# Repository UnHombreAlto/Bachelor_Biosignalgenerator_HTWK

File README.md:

# Bachelor_Biosignalgenerator_HTWK
Sammlung des Materials zur Bachelorarbeit Biosignalgenerator

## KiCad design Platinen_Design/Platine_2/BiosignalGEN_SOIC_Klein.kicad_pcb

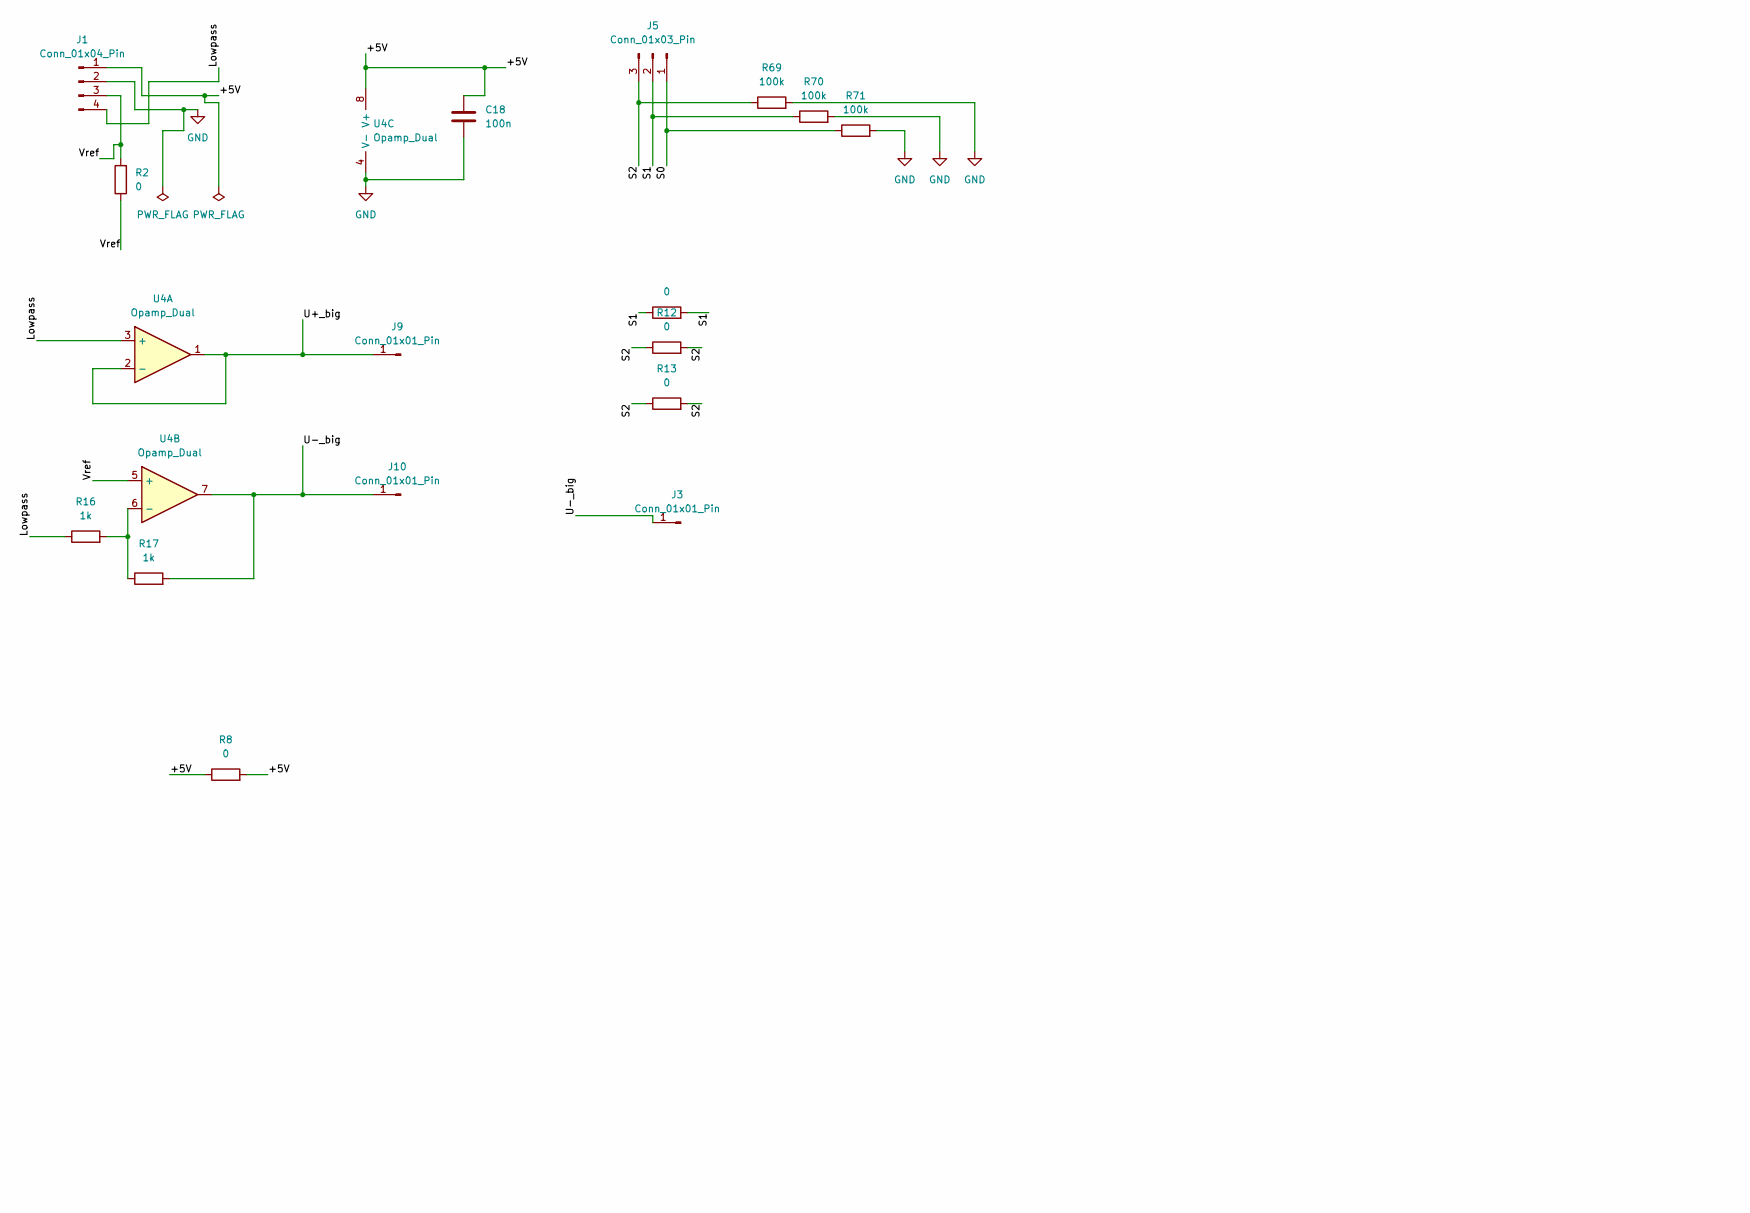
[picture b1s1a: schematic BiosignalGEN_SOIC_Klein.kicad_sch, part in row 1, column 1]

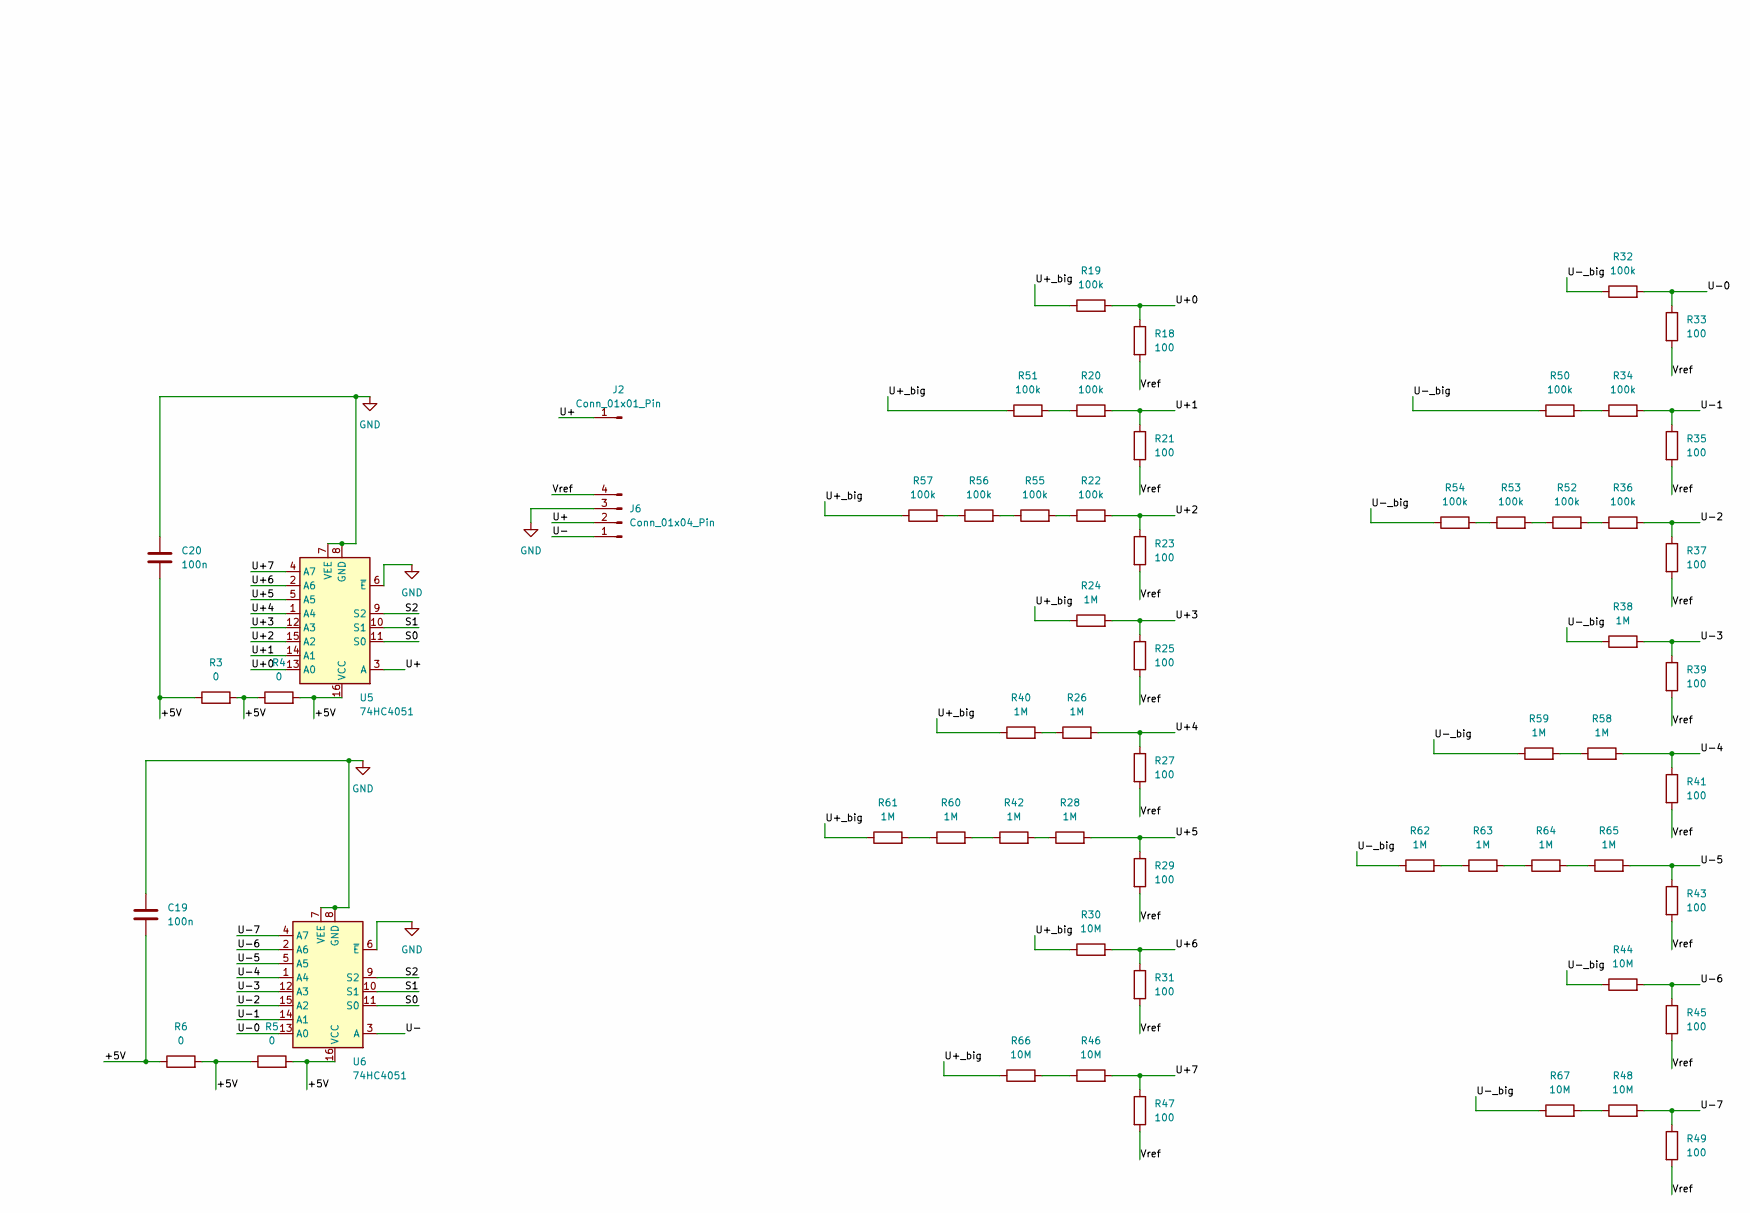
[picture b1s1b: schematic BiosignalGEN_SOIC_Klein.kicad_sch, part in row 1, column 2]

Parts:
C18, C19, C20: 100n; C_1206_3216Metric_Pad1.33x1.80mm_HandSolder
J1, J6: Conn_01x04_Pin; PinHeader_1x04_P2.54mm_Vertical
J2, J3, J9, J10: Conn_01x01_Pin; PinHeader_1x01_P2.54mm_Vertical
J5: Conn_01x03_Pin; PinHeader_1x03_P2.54mm_Vertical
R2, R3, R4, R5, R6, R8, R11, R12, R13: 0; R_1206_3216Metric_Pad1.30x1.75mm_HandSolder
R16, R17: 1k; R_1206_3216Metric_Pad1.30x1.75mm_HandSolder
R18, R21, R23, R25, R27, R29, R31, R33, R35, R37, R39, R41, R43, R45, R47, R49: 100; R_1206_3216Metric_Pad1.30x1.75mm_HandSolder
R19, R20, R22, R32, R34, R36, R50, R51, R52, R53, R54, R55, R56, R57, R69, R70, R71: 100k; R_1206_3216Metric_Pad1.30x1.75mm_HandSolder
R24, R26, R28, R38, R40, R42, R58, R59, R60, R61, R62, R63, R64, R65: 1M; R_1206_3216Metric_Pad1.30x1.75mm_HandSolder
R30, R44, R46, R48, R66, R67: 10M; R_1206_3216Metric_Pad1.30x1.75mm_HandSolder
U4: Opamp_Dual; SOIC-8_3.9x4.9mm_P1.27mm
U5, U6: 74HC4051; SO-16_3.9x9.9mm_P1.27mm

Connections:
/+5V: C18.1, C19.2, C20.2, J1.1, R3.1, R3.2, R4.1, R4.2, R5.1, R5.2, R6.1, R6.2, R8.1, R8.2, U4.8 (V+), U5.16 (VCC), U6.16 (VCC)
/Lowpass: J1.4, R16.1, U4.3 (+)
/S0: J5.1, R71.1, U5.11 (S0), U6.11 (S0)
/S1: J5.2, R11.1, R11.2, R70.1, U5.10 (S1), U6.10 (S1)
/S2: J5.3, R12.1, R12.2, R13.1, R13.2, R69.1, U5.9 (S2), U6.9 (S2)
/U+: J2.1 (Pin_1_1), J6.2, U5.3 (A)
/U+0: R18.1, R19.2, U5.13 (A0)
/U+1: R20.2, R21.1, U5.14 (A1)
/U+2: R22.2, R23.1, U5.15 (A2)
/U+3: R24.2, R25.1, U5.12 (A3)
/U+4: R26.2, R27.1, U5.1 (A4)
/U+5: R28.2, R29.1, U5.5 (A5)
/U+6: R30.2, R31.1, U5.2 (A6)
/U+7: R46.2, R47.1, U5.4 (A7)
/U+_big: J9.1 (Pin_1_1), R19.1, R24.1, R30.1, R40.1, R51.1, R57.1, R61.1, R66.1, U4.1, U4.2 (-)
/U-: J6.1, U6.3 (A)
/U-0: R32.2, R33.1, U6.13 (A0)
/U-1: R34.2, R35.1, U6.14 (A1)
/U-2: R36.2, R37.1, U6.15 (A2)
/U-3: R38.2, R39.1, U6.12 (A3)
/U-4: R41.1, R58.2, U6.1 (A4)
/U-5: R43.1, R65.2, U6.5 (A5)
/U-6: R44.2, R45.1, U6.2 (A6)
/U-7: R48.2, R49.1, U6.4 (A7)
/U-_big: J3.1 (Pin_1_1), J10.1 (Pin_1_1), R17.2, R32.1, R38.1, R44.1, R50.1, R54.1, R59.1, R62.1, R67.1, U4.7
/Vref: J1.3, J6.4, R2.1, R2.2, R18.2, R21.2, R23.2, R25.2, R27.2, R29.2, R31.2, R33.2, R35.2, R37.2, R39.2, R41.2, R43.2, R45.2, R47.2, R49.2, U4.5 (+)
GND: C18.2, C19.1, C20.1, J1.2, J6.3, R69.2, R70.2, R71.2, U4.4 (V-), U5.6 (~E), U5.7 (VEE), U5.8 (GND), U6.6 (~E), U6.7 (VEE), U6.8 (GND)
unnamed: R20.1, R51.2
unnamed: R22.1, R55.2
unnamed: R26.1, R40.2
unnamed: R28.1, R42.2
unnamed: R34.1, R50.2
unnamed: R36.1, R52.2
unnamed: R42.1, R60.2
unnamed: R46.1, R66.2
unnamed: R48.1, R67.2
unnamed: R52.1, R53.2
unnamed: R53.1, R54.2
unnamed: R55.1, R56.2
unnamed: R56.1, R57.2
unnamed: R58.1, R59.2
unnamed: R60.1, R61.2
unnamed: R62.2, R63.1
unnamed: R63.2, R64.1
unnamed: R64.2, R65.1
unnamed: R16.2, R17.1, U4.6 (-)

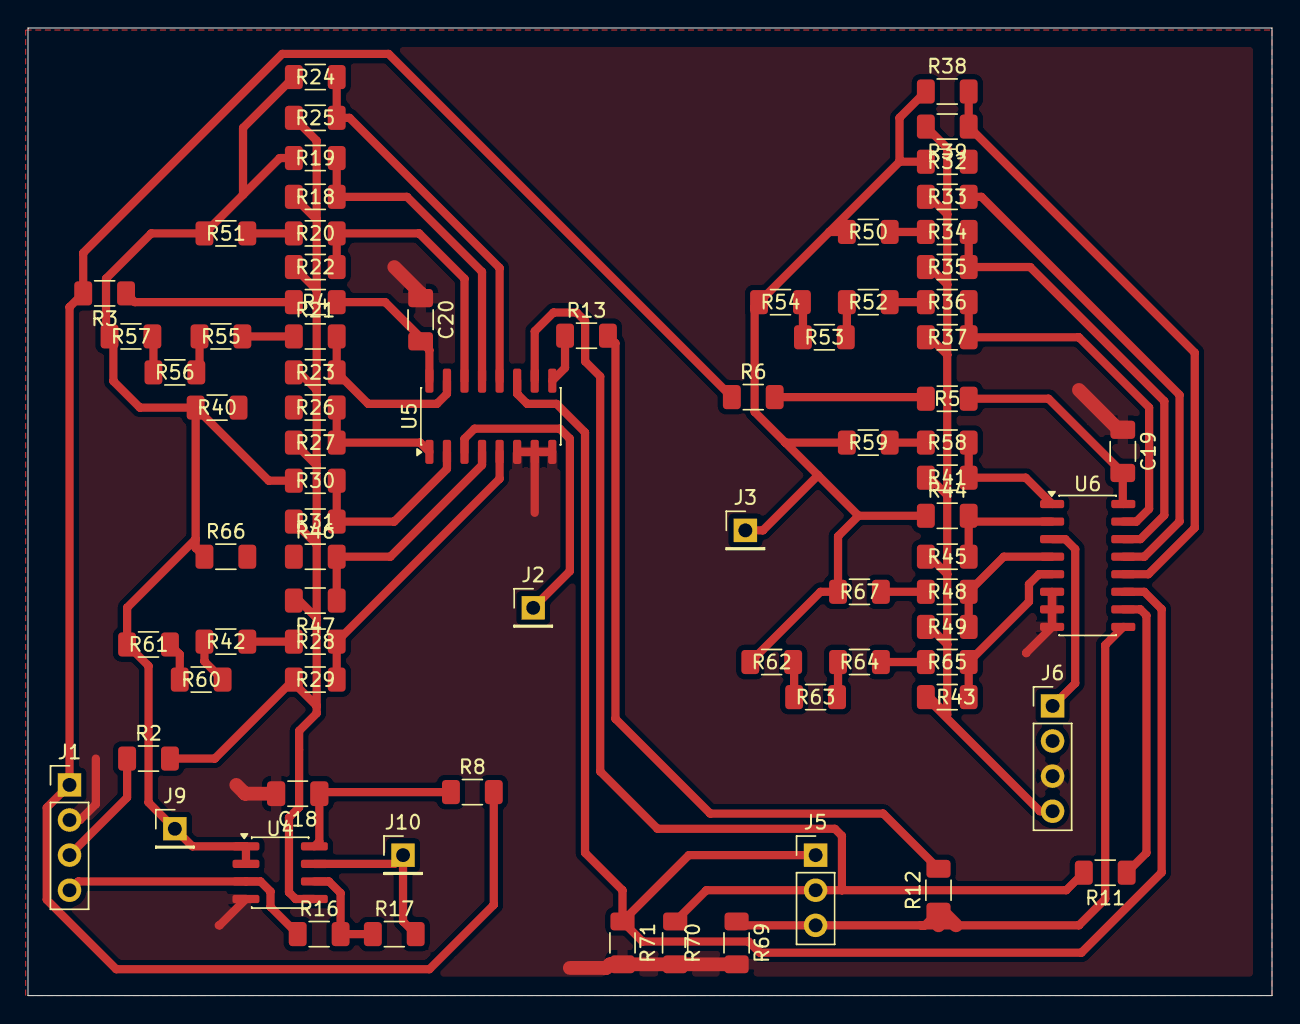
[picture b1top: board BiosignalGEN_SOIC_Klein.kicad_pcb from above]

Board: 2 copper layers, 90.0 x 70.0 mm, 77 parts (0 on the bottom side), 46 nets.

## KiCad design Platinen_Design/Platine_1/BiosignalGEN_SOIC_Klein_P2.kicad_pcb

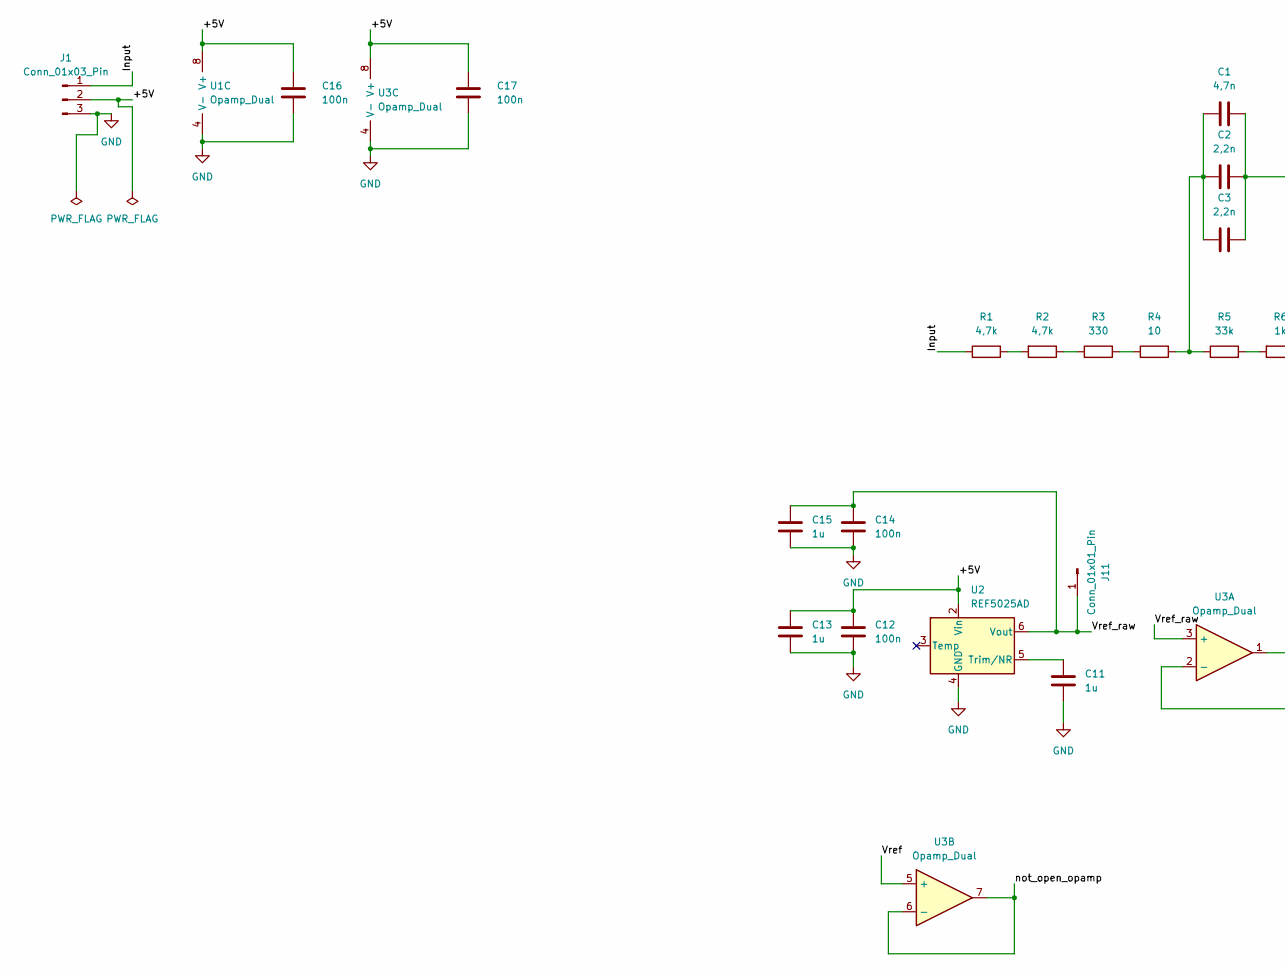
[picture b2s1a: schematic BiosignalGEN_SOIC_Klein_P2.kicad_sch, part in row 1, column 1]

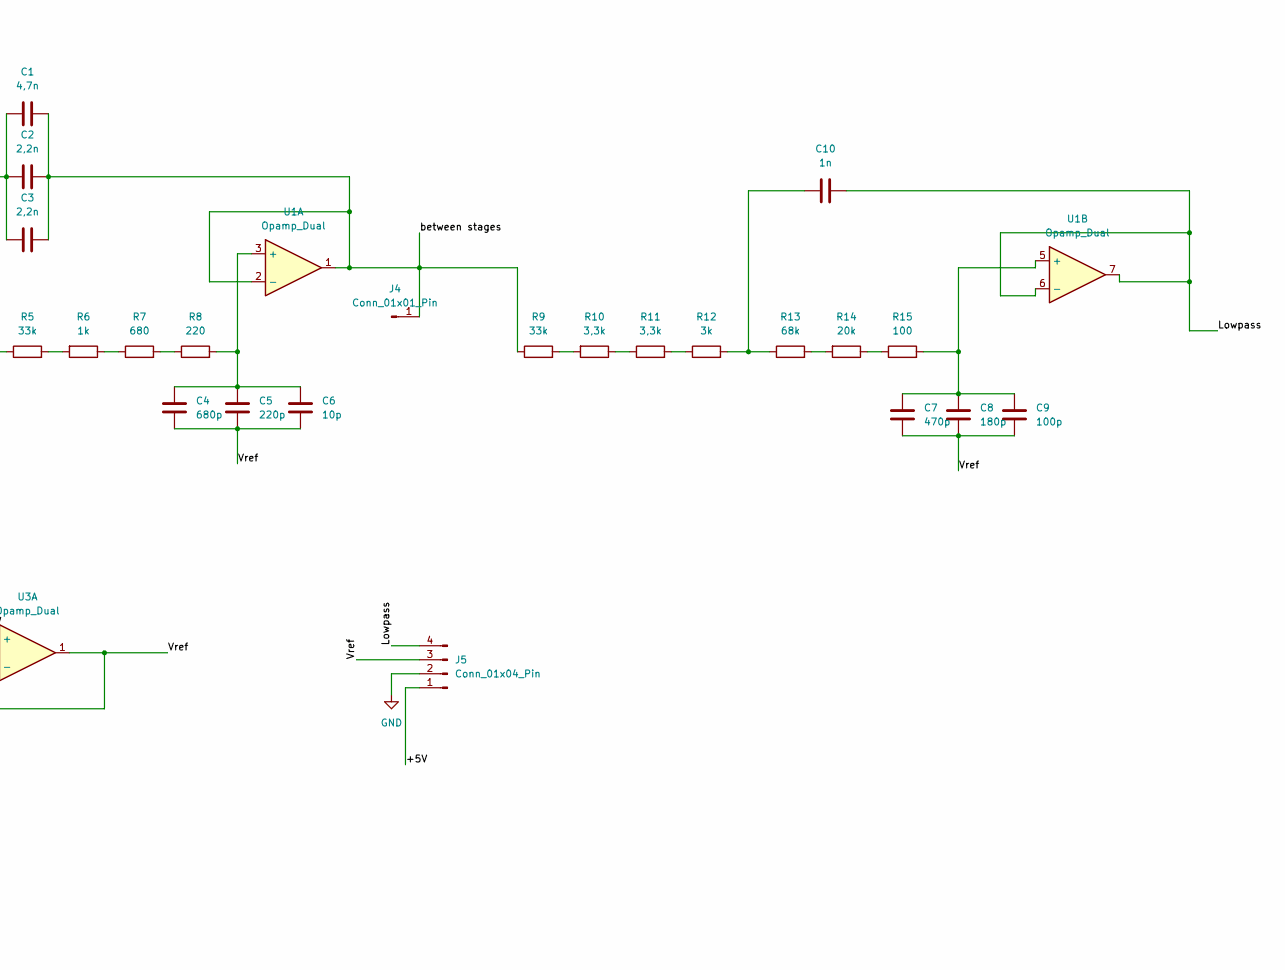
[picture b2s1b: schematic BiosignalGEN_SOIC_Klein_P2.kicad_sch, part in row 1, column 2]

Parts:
C1: 4,7n; C_1206_3216Metric_Pad1.33x1.80mm_HandSolder
C2, C3: 2,2n; C_1206_3216Metric_Pad1.33x1.80mm_HandSolder
C4: 680p; C_1206_3216Metric_Pad1.33x1.80mm_HandSolder
C5: 220p; C_1206_3216Metric_Pad1.33x1.80mm_HandSolder
C6: 10p; C_1206_3216Metric_Pad1.33x1.80mm_HandSolder
C7: 470p; C_1206_3216Metric_Pad1.33x1.80mm_HandSolder
C8: 180p; C_1206_3216Metric_Pad1.33x1.80mm_HandSolder
C9: 100p; C_1206_3216Metric_Pad1.33x1.80mm_HandSolder
C10: 1n; C_1206_3216Metric_Pad1.33x1.80mm_HandSolder
C11, C13, C15: 1u; C_1206_3216Metric_Pad1.33x1.80mm_HandSolder
C12, C14, C16, C17: 100n; C_1206_3216Metric_Pad1.33x1.80mm_HandSolder
J1: Conn_01x03_Pin; PinHeader_1x03_P2.54mm_Vertical
J4, J11: Conn_01x01_Pin; PinHeader_1x01_P2.54mm_Vertical
J5: Conn_01x04_Pin; PinHeader_1x04_P2.54mm_Vertical
R1, R2: 4,7k; R_1206_3216Metric_Pad1.30x1.75mm_HandSolder
R3: 330; R_1206_3216Metric_Pad1.30x1.75mm_HandSolder
R4: 10; R_1206_3216Metric_Pad1.30x1.75mm_HandSolder
R5, R9: 33k; R_1206_3216Metric_Pad1.30x1.75mm_HandSolder
R6: 1k; R_1206_3216Metric_Pad1.30x1.75mm_HandSolder
R7: 680; R_1206_3216Metric_Pad1.30x1.75mm_HandSolder
R8: 220; R_1206_3216Metric_Pad1.30x1.75mm_HandSolder
R10, R11: 3,3k; R_1206_3216Metric_Pad1.30x1.75mm_HandSolder
R12: 3k; R_1206_3216Metric_Pad1.30x1.75mm_HandSolder
R13: 68k; R_1206_3216Metric_Pad1.30x1.75mm_HandSolder
R14: 20k; R_1206_3216Metric_Pad1.30x1.75mm_HandSolder
R15: 100; R_1206_3216Metric_Pad1.30x1.75mm_HandSolder
U1, U3: Opamp_Dual; SOIC-8_3.9x4.9mm_P1.27mm
U2: REF5025AD; SOIC-8_3.9x4.9mm_P1.27mm

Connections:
/+5V: C12.1, C13.1, C16.1, C17.1, J1.2, J5.1, U1.8 (V+), U2.2 (Vin), U3.8 (V+)
/Input: J1.1, R1.1
/Lowpass: C10.2, J5.4, U1.6 (-), U1.7
/Vref: C4.1, C5.1, C6.1, C7.1, C8.1, C9.1, J5.3, U3.1, U3.2 (-), U3.5 (+)
/Vref_raw: C14.1, C15.1, J11.1 (Pin_1_1), U2.6 (Vout), U3.3 (+)
/between stages: C1.2, C2.2, C3.2, J4.1 (Pin_1_1), R9.1, U1.1, U1.2 (-)
/not_open_opamp: U3.6 (-), U3.7
GND: C11.2, C12.2, C13.2, C14.2, C15.2, C16.2, C17.2, J1.3, J5.2, U1.4 (V-), U2.4 (GND), U3.4 (V-)
unnamed: C1.1, C2.1, C3.1, R4.2, R5.1
unnamed: C10.1, R12.2, R13.1
unnamed: R1.2, R2.2
unnamed: R2.1, R3.1
unnamed: R3.2, R4.1
unnamed: R5.2, R6.2
unnamed: R6.1, R7.1
unnamed: R7.2, R8.1
unnamed: R10.1, R11.1
unnamed: R9.2, R10.2
unnamed: R11.2, R12.1
unnamed: R13.2, R14.2
unnamed: R14.1, R15.1
unnamed: C4.2, C5.2, C6.2, R8.2, U1.3 (+)
unnamed: C7.2, C8.2, C9.2, R15.2, U1.5 (+)
unnamed: C11.1, U2.5 (Trim/NR)

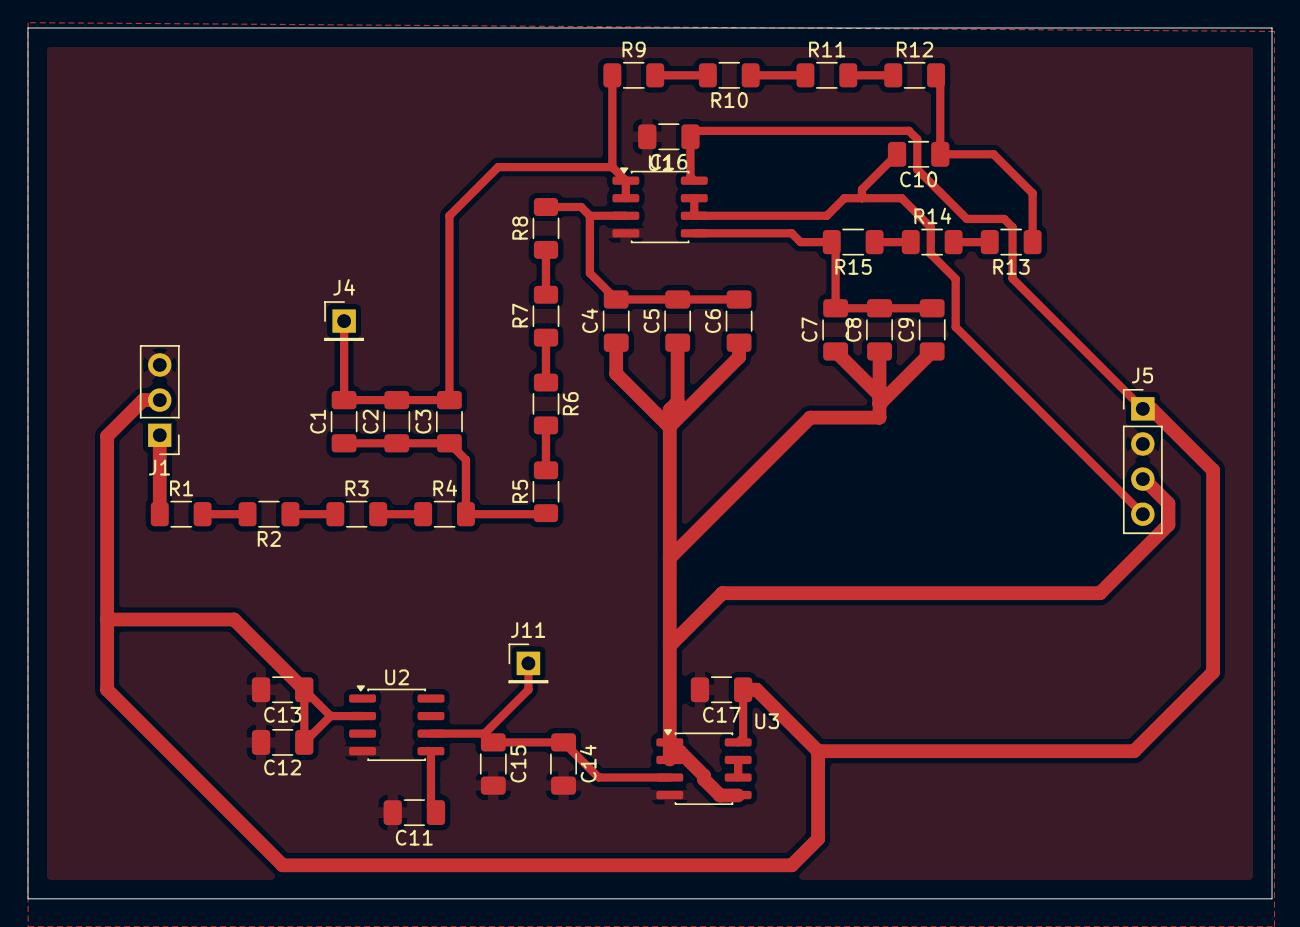
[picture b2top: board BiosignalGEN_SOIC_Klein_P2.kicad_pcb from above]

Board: 2 copper layers, 90.0 x 63.0 mm, 39 parts (0 on the bottom side), 24 nets.
